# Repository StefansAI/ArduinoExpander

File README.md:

<h1 style="text-align: center;">ArduinoExpander</h1>
<h2 style="text-align: center;">IO Expander for Arduino Uno</h2>
<br>
<div style="text-align: center;">
  
</div>
<br>
This IO expander plugs into an Arduino Uno to add more controllable pins. It can be used for instance to interact with TTL circuits. One configuration can be 24 bits output and 8 bit bi-directional. Replacing the 74HCT245 chip with a 74HCT573 will give 32 bits output only.
<br><br>
<div style="text-align: center;">
  
</div>
<br>
The schematic and layout are design with KiCad 9.
<br><br>
<div style="text-align: center;">
  
</div>
<br>

The repository contains an example code to test a RAM chip on a breadboard connected to the expander as address bus, databus and control signals.

<br><br>
<div style="text-align: center;">
  
</div>
<br>
Here is an example to test the HexDisplayController.

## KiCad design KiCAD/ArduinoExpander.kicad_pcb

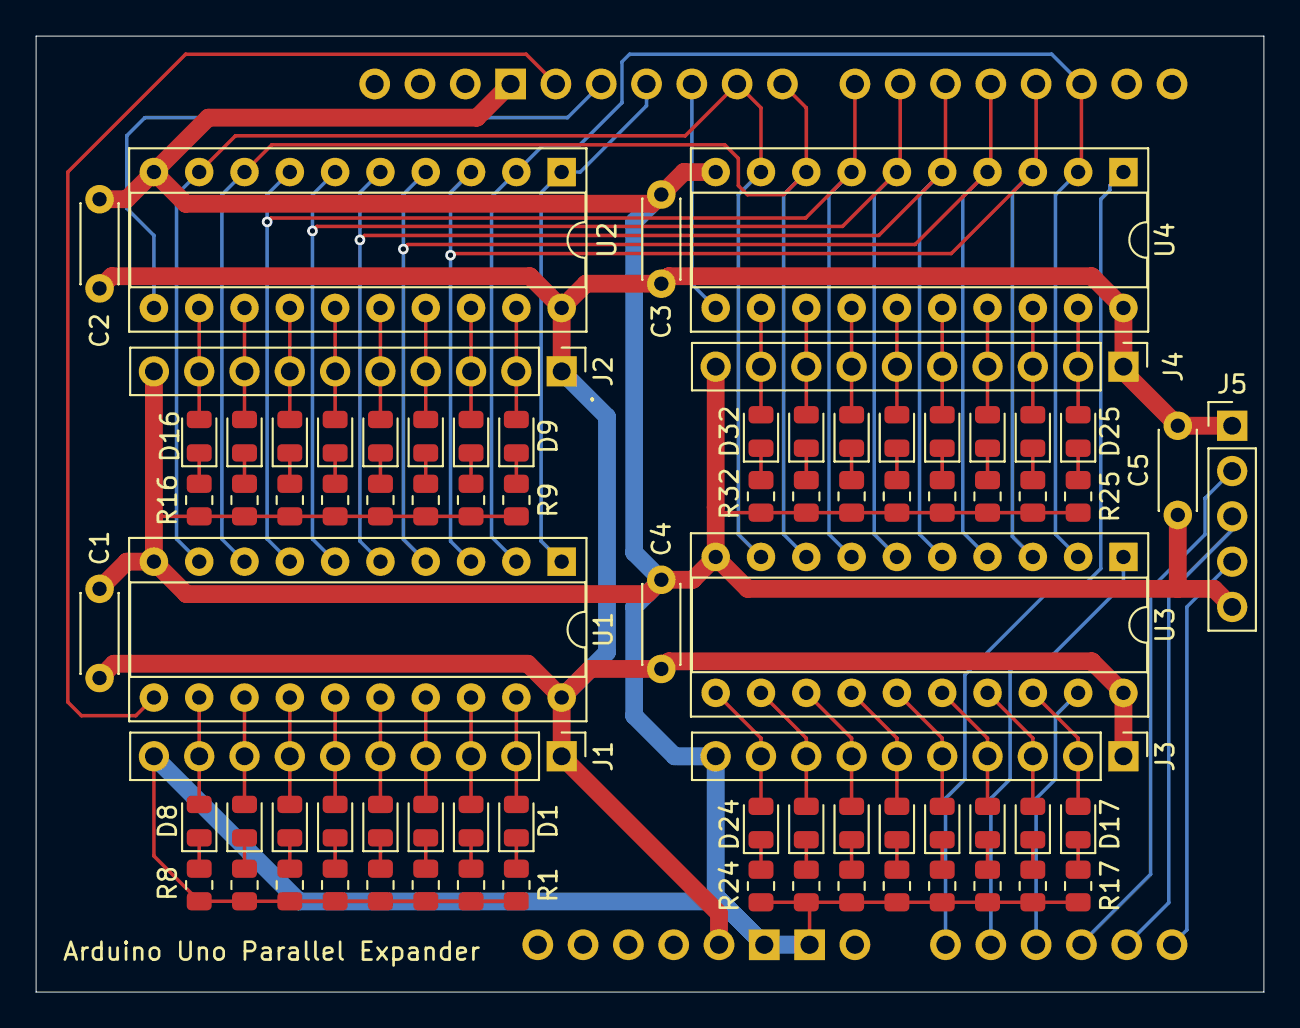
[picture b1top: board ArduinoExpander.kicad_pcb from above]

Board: 2 copper layers, 68.8 x 53.6 mm, 79 parts (0 on the bottom side), 84 nets.

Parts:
A1: Arduino_Uno_R3_Shield
C1, C2, C3, C4, C5: 100n; C_Disc_D4.3mm_W1.9mm_P5.00mm
D1, D2, D3, D4, D5, D6, D7, D8, D9, D10, D11, D12, D13, D14, D15, D16, D17, D18, D19, D20, D21, D22, D23, D24, D25, D26, D27, D28, D29, D30, D31, D32: LED; LED_0805_2012Metric
J1, J2, J3, J4: Header; PinHeader_1x10_P2.54mm_Vertical
J5: Header; PinHeader_1x05_P2.54mm_Vertical
R1, R2, R3, R4, R5, R6, R7, R8, R9, R10, R11, R12, R13, R14, R15, R16, R17, R18, R19, R20, R21, R22, R23, R24, R25, R26, R27, R28, R29, R30, R31, R32: 1k; R_0805_2012Metric
U1, U2, U4: 74LS573; DIP-20_W7.62mm_Socket
U3: 74LS245; DIP-20_W7.62mm_Socket

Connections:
+5V: A1.5V1 (5V), C1.2, C2.2, C3.2, C4.2, C5.2, J1.1, J2.1, J3.1, J4.1, J5.1, U1.20 (VCC), U2.20 (VCC), U3.20 (VCC), U4.20 (VCC)
/CTRL_0: A1.A3, J5.2
/CTRL_1: A1.A4, J5.3
/CTRL_2: A1.A5, J5.4
/DB0: A1.D2 (D2_INT0), U1.2 (D0), U2.2 (D0), U3.2 (A0), U4.2 (D0)
/DB1: A1.D3 (D3_INT1), U1.3 (D1), U2.3 (D1), U3.3 (A1), U4.3 (D1)
/DB2: A1.D4, U1.4 (D2), U2.4 (D2), U3.4 (A2), U4.4 (D2)
/DB3: A1.D5, U1.5 (D3), U2.5 (D3), U3.5 (A3), U4.5 (D3)
/DB4: A1.D6, U1.6 (D4), U2.6 (D4), U3.6 (A4), U4.6 (D4)
/DB5: A1.D7, U1.7 (D5), U2.7 (D5), U3.7 (A5), U4.7 (D5)
/DB6: A1.D8, U1.8 (D6), U2.8 (D6), U3.8 (A6), U4.8 (D6)
/DB7: A1.D9, U1.9 (D7), U2.9 (D7), U3.9 (A7), U4.9 (D7)
/LE_A_PIN: A1.D13, U1.11 (Load)
/LE_B_PIN: A1.D12, U2.11 (Load)
/LE_D_PIN: A1.D10 (D10_CS), U4.11 (Load)
/OE_AB_PIN: A1.D11, U1.1 (OE), U2.1 (OE)
/PIN1_C_PIN: A1.A1, U3.1 (A->B)
/PIN1_D_PIN: A1.A0, U4.1 (OE)
/PIN19_C_PIN: A1.A2, U3.19 (CE)
GND: A1.GND1 (GND), A1.GND2 (GND), A1.GND3 (GND), C1.1, C2.1, C3.1, C4.1, C5.1, J1.10, J2.10, J3.10, J4.10, J5.5, R1.2, R2.2, R3.2, R4.2, R5.2, R6.2, R7.2, R8.2, R9.2, R10.2, R11.2, R12.2, R13.2, R14.2, R15.2, R16.2, R17.2, R18.2, R19.2, R20.2, R21.2, R22.2, R23.2, R24.2, R25.2, R26.2, R27.2, R28.2, R29.2, R30.2, R31.2, R32.2, U1.10 (GND), U2.10 (GND), U3.10 (GND), U4.10 (GND)
unnamed: D1.2 (A), J1.2, U1.19 (Q0)
unnamed: D1.1 (K), R1.1
unnamed: D2.2 (A), J1.3, U1.18 (Q1)
unnamed: D2.1 (K), R2.1
unnamed: D3.2 (A), J1.4, U1.17 (Q2)
unnamed: D3.1 (K), R3.1
unnamed: D4.2 (A), J1.5, U1.16 (Q3)
unnamed: D4.1 (K), R4.1
unnamed: D5.2 (A), J1.6, U1.15 (Q4)
unnamed: D5.1 (K), R5.1
unnamed: D6.2 (A), J1.7, U1.14 (Q5)
unnamed: D6.1 (K), R6.1
unnamed: D7.2 (A), J1.8, U1.13 (Q6)
unnamed: D7.1 (K), R7.1
unnamed: D8.2 (A), J1.9, U1.12 (Q7)
unnamed: D8.1 (K), R8.1
unnamed: D9.2 (A), J2.2, U2.19 (Q0)
unnamed: D9.1 (K), R9.1
unnamed: D10.2 (A), J2.3, U2.18 (Q1)
unnamed: D10.1 (K), R10.1
unnamed: D11.2 (A), J2.4, U2.17 (Q2)
unnamed: D11.1 (K), R11.1
unnamed: D12.2 (A), J2.5, U2.16 (Q3)
unnamed: D12.1 (K), R12.1
unnamed: D13.2 (A), J2.6, U2.15 (Q4)
unnamed: D13.1 (K), R13.1
unnamed: D14.2 (A), J2.7, U2.14 (Q5)
unnamed: D14.1 (K), R14.1
unnamed: D15.2 (A), J2.8, U2.13 (Q6)
unnamed: D15.1 (K), R15.1
unnamed: D16.2 (A), J2.9, U2.12 (Q7)
unnamed: D16.1 (K), R16.1
unnamed: D17.2 (A), J3.2, U3.18 (B0)
unnamed: D17.1 (K), R17.1
unnamed: D18.2 (A), J3.3, U3.17 (B1)
unnamed: D18.1 (K), R18.1
unnamed: D19.2 (A), J3.4, U3.16 (B2)
unnamed: D19.1 (K), R19.1
unnamed: D20.2 (A), J3.5, U3.15 (B3)
unnamed: D20.1 (K), R20.1
unnamed: D21.2 (A), J3.6, U3.14 (B4)
unnamed: D21.1 (K), R21.1
unnamed: D22.2 (A), J3.7, U3.13 (B5)
unnamed: D22.1 (K), R22.1
unnamed: D23.2 (A), J3.8, U3.12 (B6)
unnamed: D23.1 (K), R23.1
unnamed: D24.2 (A), J3.9, U3.11 (B7)
unnamed: D24.1 (K), R24.1
unnamed: D25.2 (A), J4.2, U4.19 (Q0)
unnamed: D25.1 (K), R25.1
unnamed: D26.2 (A), J4.3, U4.18 (Q1)
unnamed: D26.1 (K), R26.1
unnamed: D27.2 (A), J4.4, U4.17 (Q2)
unnamed: D27.1 (K), R27.1
unnamed: D28.2 (A), J4.5, U4.16 (Q3)
unnamed: D28.1 (K), R28.1
unnamed: D29.2 (A), J4.6, U4.15 (Q4)
unnamed: D29.1 (K), R29.1
unnamed: D30.2 (A), J4.7, U4.14 (Q5)
unnamed: D30.1 (K), R30.1
unnamed: D31.2 (A), J4.8, U4.13 (Q6)
unnamed: D31.1 (K), R31.1
unnamed: D32.2 (A), J4.9, U4.12 (Q7)
unnamed: D32.1 (K), R32.1

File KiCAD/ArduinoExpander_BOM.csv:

"Reference","Value","Datasheet","Footprint","Qty","DNP","OrderInfo"
"A1","Arduino_Uno_R3_Shield","https://docs.arduino.cc/hardware/uno-rev3","footprints:Arduino_Uno_R3_Shield","1","","https://www.amazon.com/ELEGOO-Board-ATmega328P-ATMEGA16U2-Co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"
"C1,C2,C3,C4,C5","100n","~","Capacitor_THT:C_Disc_D4.3mm_W1.9mm_P5.00mm","5","","https://www.digikey.com/en/products/detail/kemet/C320C104M5R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"
"D1,D2,D3,D4,D5,D6,D7,D8,D9,D10,D11,D12,D13,D14,D15,D16,D17,D18,D19,D20,D21,D22,D23,D24,D25,D26,D27,D28,D29,D30,D31,D32","LED","~","LED_SMD:LED_0805_2012Metric","32","","https://www.digikey.com/en/products/detail/harvatek-corporat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"
"J1,J2,J3,J4,J5","Header","~","Connector_PinHeader_2.54mm:PinHeader_1x05_P2.54mm_Vertical,Connector_PinHeader_2.54mm:PinHeader_1x10_P2.54mm_Vertical","5","",""
"R1,R2,R3,R4,R5,R6,R7,R8,R9,R10,R11,R12,R13,R14,R15,R16,R17,R18,R19,R20,R21,R22,R23,R24,R25,R26,R27,R28,R29,R30,R31,R32","1k","~","Resistor_SMD:R_0805_2012Metric","32","","https://www.digikey.com/en/products/detail/yageo/RC0805FR-07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"
"U1,U2,U4","74HCT573","74xx/74hc573.pdf","Package_DIP:DIP-20_W7.62mm_Socket","3","","https://www.digikey.com/en/products/detail/texas-instruments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"
"U3","74HCT245","http://www.ti.com/lit/gpn/sn74LS245","Package_DIP:DIP-20_W7.62mm_Socket","1","","https://www.digikey.com/en/products/detail/texas-instruments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"

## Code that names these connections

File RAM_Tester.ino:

// ================================================
//
// SPDX-FileCopyrightText: 2025 Stefan Warnke
//
// SPDX-License-Identifier: BeerWare
//
//=================================================
//
// File:  RAM_Tester
// 
// The code can be used to test a number of 
// different circuitries, like logic chips, RAMs, 
// ROMs etc with the Arduino ExpansionBoard
//
//=================================================

// General ExpansionBoard pin definitions
//---------------------------------------
// Definition of the D0 pin
const int DATA_PIN_D0 = 2;
// Output enable for AB outputs
const int OE_AB_PIN = 11;
// Latch enable for A register
const int LE_A_PIN = 13;
// Latch enable for B register
const int LE_B_PIN = 12;
// Output enable for D register
const int PIN1_D_PIN = A0;   
// Direction signal for 74HCT245 type chip
const int PIN1_C_PIN = A1;   
// Output enable for C register or 74HCT245 buffer
const int PIN19_C_PIN = A2;   
// Latch enable for D register
const int LE_D_PIN = 10; 
// J5 Header control line 0     
const int CTRL_0 = A3;   
// J5 Header control line 1    
const int CTRL_1 = A4;   
// J5 Header control line 2
const int CTRL_2 = A5;    

// RAM tester specific pin definitions
//---------------------------------------
// RAM Write Enable pin
const int WE_PIN = CTRL_0; 
// RAM Chip Select pin    
const int CS_PIN = CTRL_1;    
// RAM Output Enable pin 
const int OE_PIN = CTRL_2;      

// Masks to set or reset the control signals
const int RAM_CS_H = 1<<0;
const int RAM_OE_H = 1<<1;
const int RAM_WE_H = 1<<2;
const int RAM_CS_L = 0;
const int RAM_OE_L = 0;
const int RAM_WE_L = 0;

// Example max addr for a HM62256
const int MAX_ADDR = (1<<15)-1;

// Buffer for sprintf
char buff[100];
// Variable for address output
int addr = 0; //0x33A0;
// Variable for data output 
int wr_data = 0;
// Variable for data input
int rd_data = 0;
// Cycle counter
int cycle = 0;
// Control signals
int ctrl = 0;

// Set the 8 bit data output for any register
void set_data(int value)
{
  for (int i=0; i<8; i++)
  {
    if ((value & 1) == 0)
      digitalWrite(DATA_PIN+i, LOW);
    else
      digitalWrite(DATA_PIN+i, HIGH);
    value >>= 1;
  }
}

// Read data input
int get_data()
{
  int result=0;
  for (int i=0; i<8; i++)
  {
    int value = digitalRead(DATA_PIN+i);
    if (value == HIGH)
      result += 1<<i;    
  }
  return result;
}

// Set data to output mode
void set_data_out()
{
   for (int i=DATA_PIN; i<DATA_PIN+8; i++)
      pinMode(i, OUTPUT);  
}

// Set data to input mode
void set_data_in()
{
  for (int i=DATA_PIN; i<DATA_PIN+8; i++)
      pinMode(i, INPUT);  
}

// Set the pin output level
void set_pin_out(int pin, int level)
{
  pinMode(pin, OUTPUT);
  digitalWrite(pin, level);
}

// Write a value to the A register
void set_A(int value)
{
  set_data_out();
  set_data(value);
  digitalWrite(LE_A_PIN, HIGH);
  digitalWrite(LE_A_PIN, LOW);
  digitalWrite(OE_AB_PIN, LOW);
}

// Write a value to the B register
void set_B(int value)
{
  set_data_out();
  set_data(value);
  digitalWrite(LE_B_PIN, HIGH);
  digitalWrite(LE_B_PIN, LOW);
  digitalWrite(OE_AB_PIN, LOW);
}

// Write a value to the D register
void set_D(int value)
{
  set_data_out();
  set_data(value);
  digitalWrite(LE_D_PIN, HIGH);
  digitalWrite(LE_D_PIN, LOW);
  digitalWrite(PIN1_D_PIN, LOW);
}

// Write a value to the C channel (DB)
void set_Cout(int value)
{
  set_data_out();
  set_data(value);
  digitalWrite(PIN1_C_PIN, HIGH);
  digitalWrite(PIN19_C_PIN, LOW);
}

// Read a value from the C channel (DB)
int get_Cin()
{
  set_data_in();
  digitalWrite(PIN1_C_PIN, LOW);
  digitalWrite(PIN19_C_PIN, LOW);
  int result = get_data();
  digitalWrite(PIN19_C_PIN, HIGH);
  return result;
}

// Setup the pins for the main loop
void setup() 
{
  Serial.begin(9600);
  set_data_out();
  set_pin_out(OE_AB_PIN, HIGH);
  set_pin_out(LE_A_PIN, HIGH);
  set_pin_out(LE_B_PIN, HIGH);
  set_pin_out(PIN1_D_PIN, HIGH);
  set_pin_out(PIN1_C_PIN, HIGH);
  set_pin_out(PIN19_C_PIN, HIGH);
  set_pin_out(LE_D_PIN, HIGH);
  set_pin_out(WE_PIN,HIGH);
  set_pin_out(CS_PIN,HIGH);
  set_pin_out(OE_PIN,HIGH);

/*WritePattern();

    digitalWrite(PIN19_C_PIN, HIGH);
    set_D(RAM_CS_H | RAM_OE_H | RAM_WE_H);
    set_A(addr & 0xFF);
    set_B(addr >> 8);
    set_Cout(wr_data);
*/
  Serial.println("Setup Done");
}

#define TIME 1000

// Write a pseudo random pattern
void WritePattern()
{
  sprintf(buff,"Writing cycle=%d", cycle); 
  Serial.println(buff);

  for (addr=0; addr<MAX_ADDR; addr++)
  {
     wr_data = ((addr & 0xFF)) ^ (addr >> 8) ^ cycle) & 0xFF;
    //wr_data = 1<<(i & 7);
 
    //sprintf(buff,"Writing cycle=%d  addr=%04X  wr_data=%02X", cycle, addr, wr_data); 
    //Serial.println(buff);

    digitalWrite(PIN19_C_PIN, HIGH);
    set_A(addr & 0xFF);
    set_B(addr >> 8);
    set_Cout(wr_data);
    digitalWrite(CS_PIN,LOW);
    digitalWrite(WE_PIN,LOW);
    digitalWrite(WE_PIN,HIGH);
    digitalWrite(CS_PIN,HIGH);
    digitalWrite(PIN19_C_PIN, HIGH);
    //delay(TIME);
  }
}

// Read and check the pseudo random pattern
void CheckPattern()
{
  Serial.println("Loop Reading");

  for (addr=0; addr<MAX_ADDR; addr++)
  {
    wr_data = ((addr & 0xFF)) ^ (addr >> 8) ^ cycle) &0xFF;
    //wr_data = 1<<(addr & 7);
 
    digitalWrite(PIN19_C_PIN, HIGH);
    set_A(addr & 0xFF);
    set_B(addr >> 8);
    digitalWrite(CS_PIN,LOW);
    digitalWrite(OE_PIN,LOW);
    rd_data = get_Cin();
    digitalWrite(OE_PIN,HIGH);
    digitalWrite(CS_PIN,HIGH);
    if (rd_data != wr_data)
    {
      sprintf(buff,"Reading cycle=%d  addr=%04X  wr_data=%02X  rd_data=%02X", cycle, addr, wr_data, rd_data); 
      Serial.println(buff);
      delay(TIME);
    }
  }
}


// Another way of testing
void Test1()
{
  sprintf(buff,"addr=%04X", addr); 
  Serial.println(buff);
  set_A(addr & 0xFF);
  set_B(addr >> 8);
  set_D(ctrl);
  set_Cout(wr_data);
  delay(500);
  ctrl = ctrl >> 1;
  if ((ctrl & 0xFF) == 0)
    ctrl = 0x80;
  wr_data = wr_data << 1;
  if ((wr_data & 0xFF) == 0)
    wr_data = 1;
  addr=addr+1;
}

// Another possible Test run
void Test1()
{

  //set_D(RAM_CS_H | RAM_OE_H | RAM_WE_H);
  //rd_data = get_Cin();

  for (i=0; i<8; i++)
  {
    wr_data = 1<<(i & 7);

      sprintf(buff,"Writing cycle=%d  wr_data=%02X", cycle, wr_data); 
      Serial.println(buff);

    set_Cout(wr_data);
    delay(TIME);
    
    rd_data = get_Cin();

      sprintf(buff,"Reading cycle=%d  rd_data=%02X", cycle, rd_data); 
      Serial.println(buff);

    delay(TIME);
  }
}

// Main loop
void loop() 
{
  WritePattern();
  CheckPattern();
   cycle++;
}

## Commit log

2025-09-10 Initial Check-in
